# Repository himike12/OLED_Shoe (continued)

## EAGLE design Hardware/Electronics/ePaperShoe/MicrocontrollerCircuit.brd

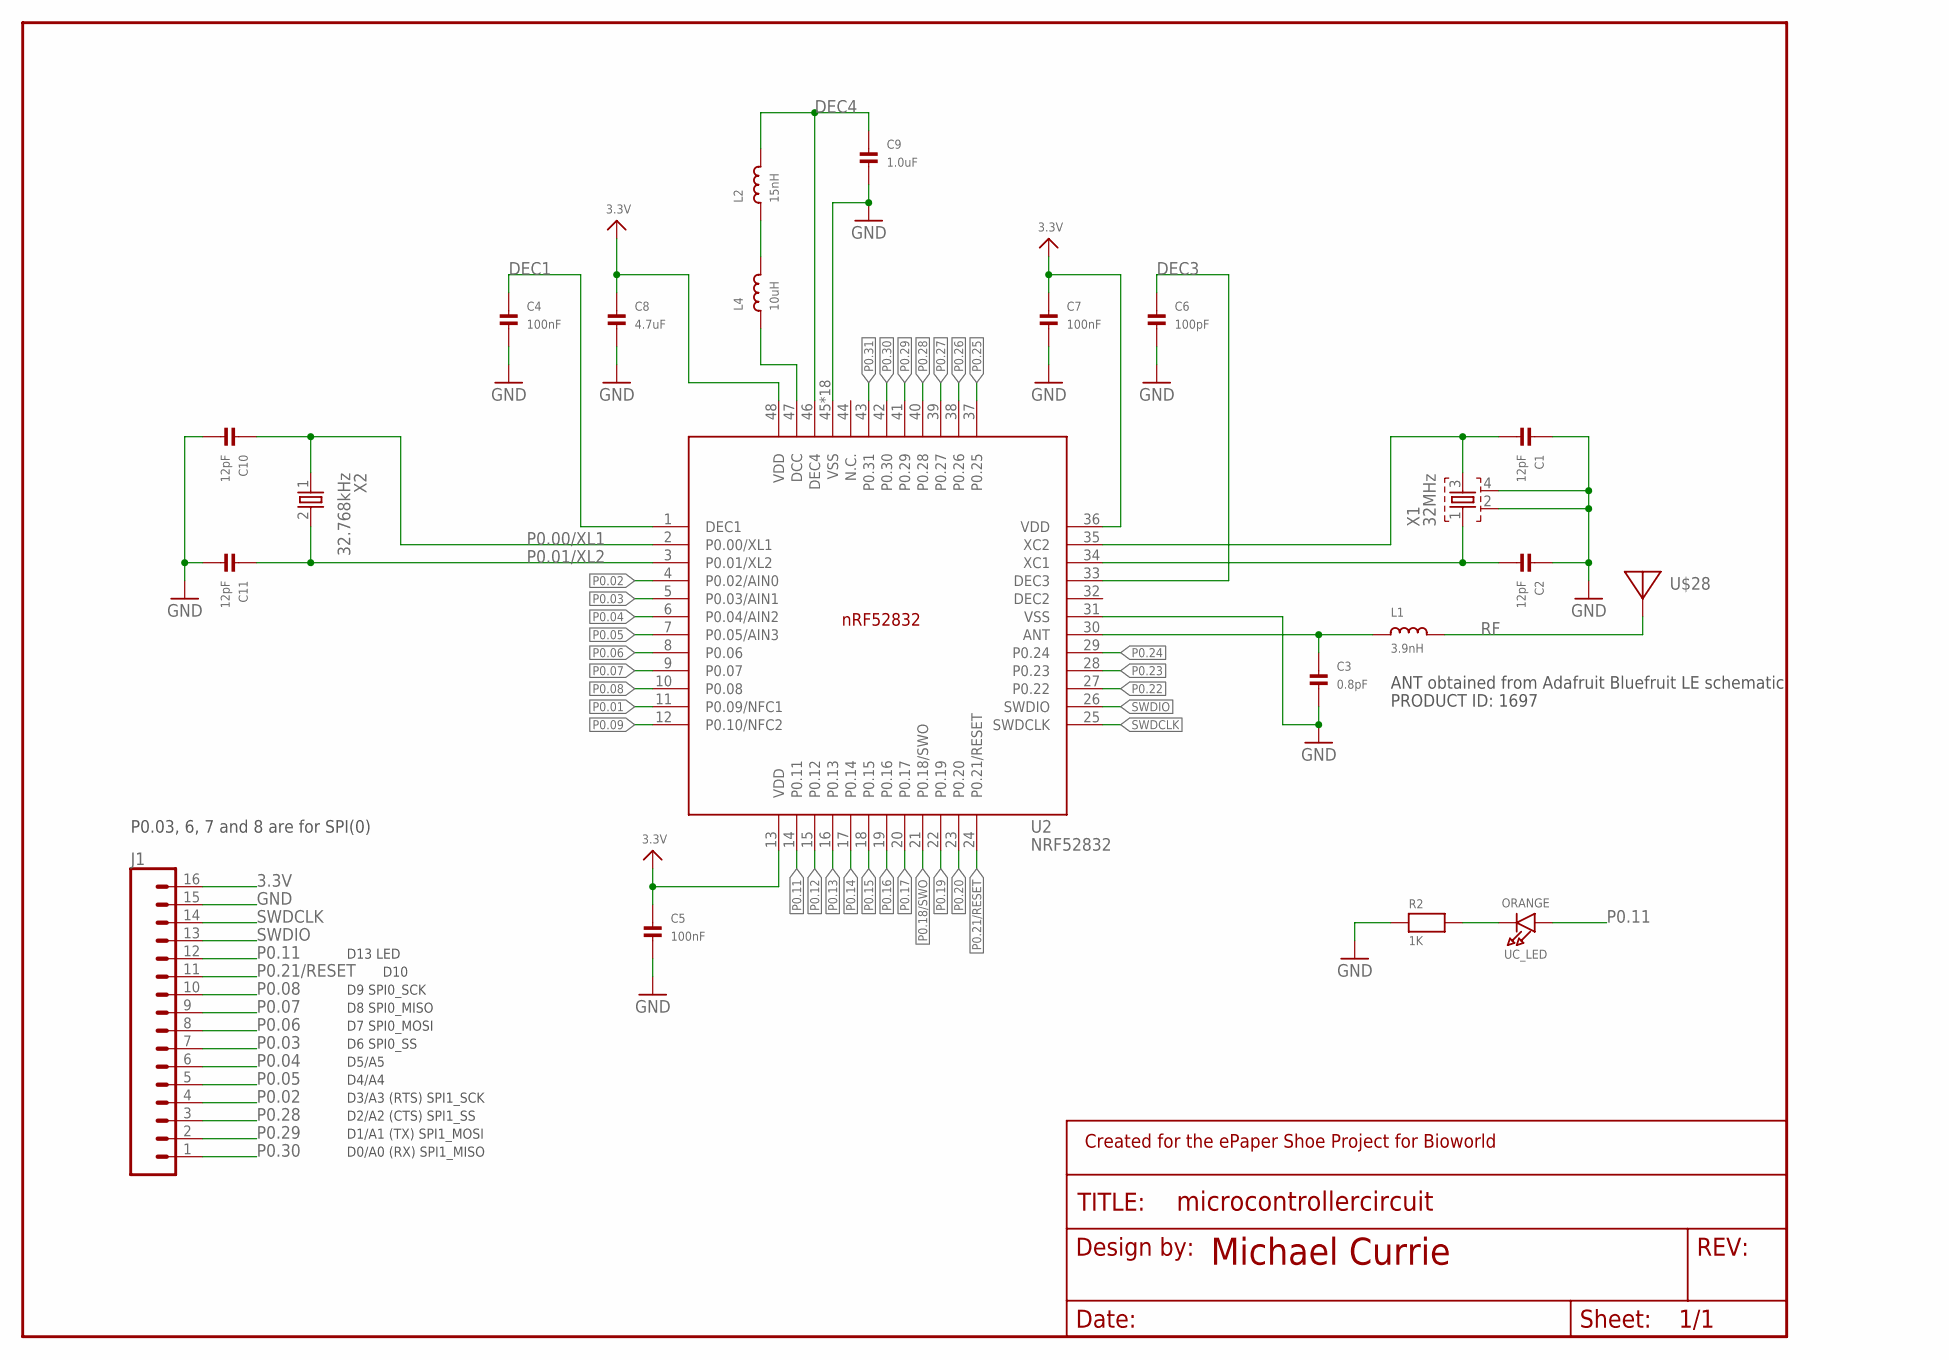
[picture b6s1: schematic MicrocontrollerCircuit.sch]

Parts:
C1, C2, C10, C11: 12pF; 1206
C3: 0.8pF; 1206
C4, C5, C7: 100nF; 1206
C6: 100pF; 1206
C8: 4.7uF; 1206
C9: 1.0uF; 1206
FRAME2: FRAME-LETTER-MICHAELNO_PACKAGE; DUMMY
J1: CONN_16; 1X16
L1: 3.9nH; 0805
L2: 15nH; 0805
L4: 10uH; 0805
R2: 1K; 0805
U2: NRF52832; QFN40P600X600X90-48_N
U$28: ANTENNA_PCBNRF8001_1.6MM; ANT_PCB_2.4GHZ_NRF8001_1.6MM_1OZ
UC_LED: ORANGE; CHIPLED_0805_NOOUTLINE
X1: 32MHz; BT-XTAL_2016_N
X2: 32.768kHz; XTAL_3215_N

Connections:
3.3V: C5.1, C7.1, C8.1, J1.16, U2.13 (VDD), U2.36 (VDD), U2.48 (VDD)
ANT: C3.1, L1.1, U2.30 (ANT)
DEC1: C4.1, U2.1 (DEC1)
DEC3: C6.1, U2.33 (DEC3)
DEC4: C9.1, L2.2, U2.46 (DEC4)
GND: C1.1, C2.1, C3.2, C4.2, C5.2, C6.2, C7.2, C8.2, C9.2, C10.2, C11.2, J1.15, R2.1, U2.31 (VSS), U2.45 (VSS), U2.PAD (VSS), U2.PAD@VIA01 (VSS), U2.PAD@VIA02 (VSS), U2.PAD@VIA03 (VSS), U2.PAD@VIA04 (VSS), U2.PAD@VIA05 (VSS), U2.PAD@VIA06 (VSS), U2.PAD@VIA07 (VSS), U2.PAD@VIA08 (VSS), U2.PAD@VIA09 (VSS), U2.PAD@VIA10 (VSS), U2.PAD@VIA11 (VSS), U2.PAD@VIA12 (VSS), U2.PAD@VIA13 (VSS), U2.PAD@VIA14 (VSS), U2.PAD@VIA15 (VSS), U2.PAD@VIA16 (VSS), X1.2, X1.4
unnamed: L2.1, L4.2
unnamed: C1.2, U2.35 (XC2), X1.3
unnamed: L4.1, U2.47 (DCC)
unnamed: R2.2, UC_LED.C
P0.00/XL1: C10.1, U2.2 (P0.00/XL1), X2.1
P0.01: U2.11 (P0.09/NFC1)
P0.01/XL2: C11.1, U2.3 (P0.01/XL2), X2.2
P0.02: J1.4, U2.4 (P0.02/AIN0)
P0.03: J1.7, U2.5 (P0.03/AIN1)
P0.04: J1.6, U2.6 (P0.04/AIN2)
P0.05: J1.5, U2.7 (P0.05/AIN3)
P0.06: J1.8, U2.8 (P0.06)
P0.07: J1.9, U2.9 (P0.07)
P0.08: J1.10, U2.10 (P0.08)
P0.09: U2.12 (P0.10/NFC2)
P0.11: J1.12, U2.14 (P0.11), UC_LED.A
P0.12: U2.15 (P0.12)
P0.13: U2.16 (P0.13)
P0.14: U2.17 (P0.14)
P0.15: U2.18 (P0.15)
P0.16: U2.19 (P0.16)
P0.17: U2.20 (P0.17)
P0.18/SWO: U2.21 (P0.18/SWO)
P0.19: U2.22 (P0.19)
P0.20: U2.23 (P0.20)
P0.21/RESET: J1.11, U2.24 (P0.21/RESET)
P0.22: U2.27 (P0.22)
P0.23: U2.28 (P0.23)
P0.24: U2.29 (P0.24)
P0.25: U2.37 (P0.25)
P0.26: U2.38 (P0.26)
P0.27: U2.39 (P0.27)
P0.28: J1.3, U2.40 (P0.28)
P0.29: J1.2, U2.41 (P0.29)
P0.30: J1.1, U2.42 (P0.30)
P0.31: U2.43 (P0.31)
RF: L1.2, U$28.FEED
SWDCLK: J1.14, U2.25 (SWDCLK)
SWDIO: J1.13, U2.26 (SWDIO)
X1: C2.2, U2.34 (XC1), X1.1

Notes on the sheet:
P0.03, 6, 7 and 8 are for SPI(0)
ANT obtained from Adafruit Bluefruit LE schematic
PRODUCT ID: 1697
D1/A1 (TX) SPI1_MOSI
D0/A0 (RX) SPI1_MISO
D2/A2 (CTS) SPI1_SS
D3/A3 (RTS) SPI1_SCK
D4/A4
D5/A5
D6 SPI0_SS
D7 SPI0_MOSI
D8 SPI0_MISO
D9 SPI0_SCK
D10
D13 LED

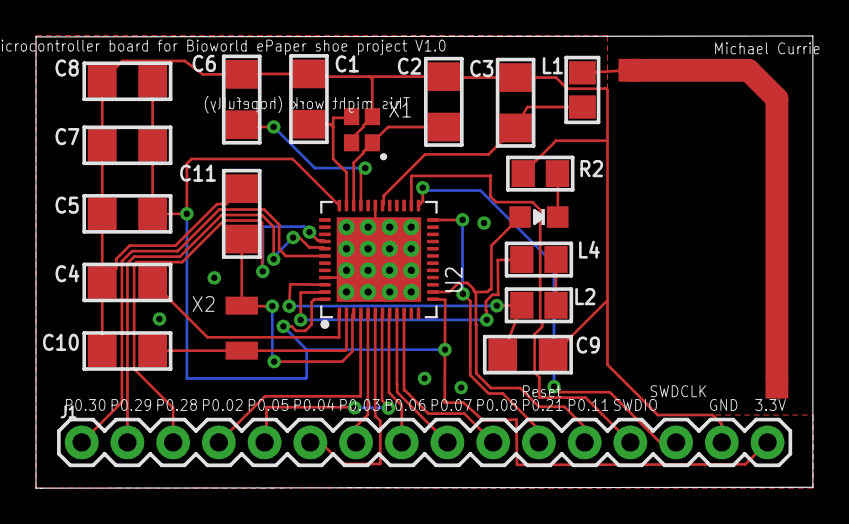
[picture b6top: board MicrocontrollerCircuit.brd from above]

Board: 2 copper layers, 43.2 x 25.1 mm, 22 parts (0 on the bottom side), 28 nets.

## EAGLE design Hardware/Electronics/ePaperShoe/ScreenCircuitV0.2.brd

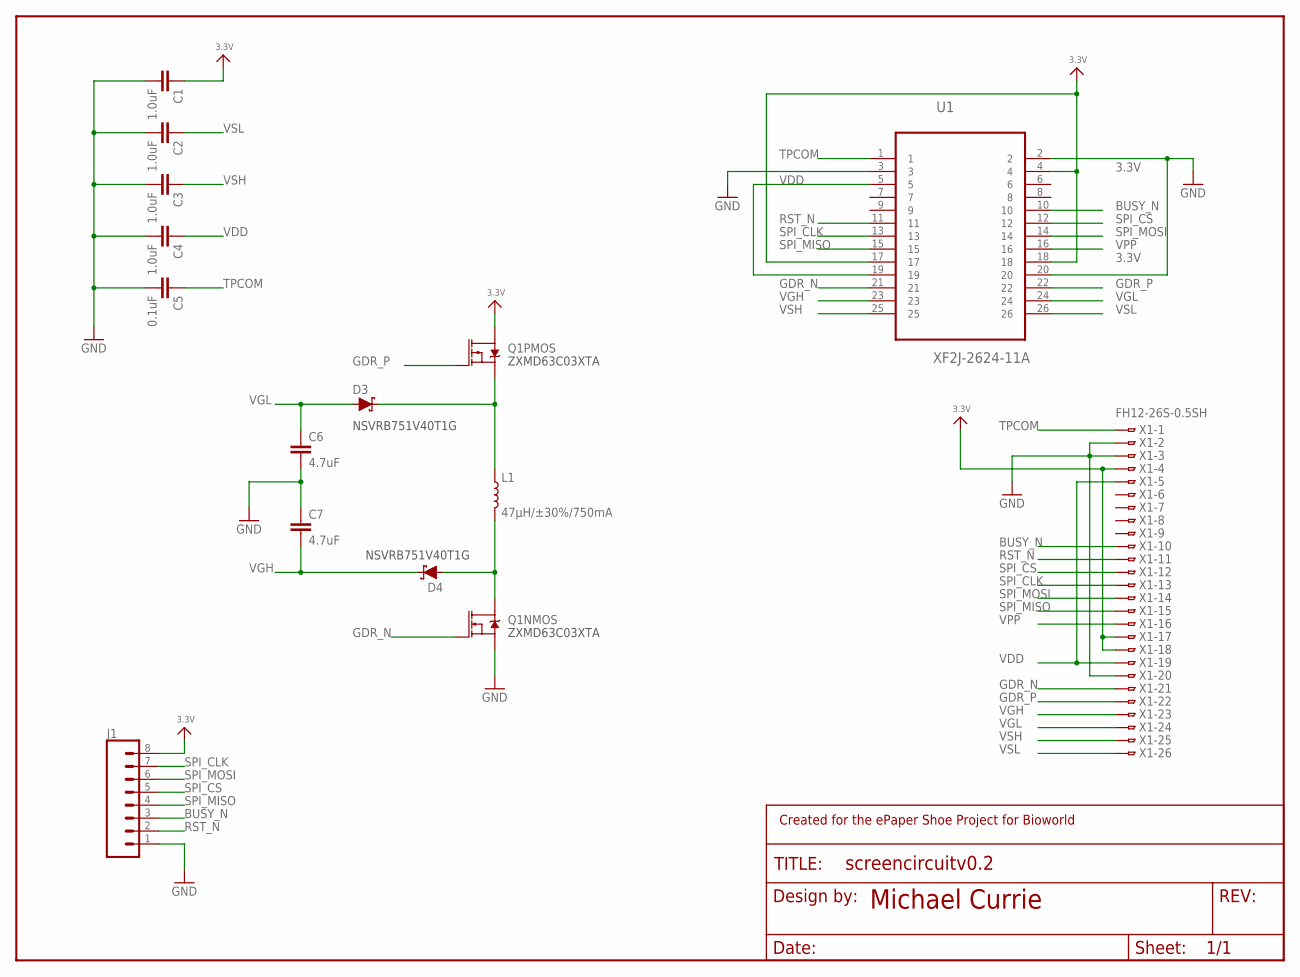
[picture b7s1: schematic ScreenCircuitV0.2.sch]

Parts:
C1, C2, C3, C4: 1.0uF; 1206
C5: 0.1uF; 0603
C6, C7: 4.7uF; 1206
D3, D4: 0.5A/40V/420mV; SOD-323
FRAME1: FRAME-LETTER-MICHAELNO_PACKAGE; DUMMY
J1: CONN_08"; 1X08
L1: 47µH/±30%/750mA; CR54
Q1: IRF7509; MSOP8
U1: XF2J-2624-11A; OMRON_XF2J-2624-11A
X1: FH12-26S-0.5SH

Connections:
3.3V: C1.1, J1.8, Q1.5 (D), Q1.6 (D), U1.4, U1.17, U1.18, X1.4, X1.17, X1.18
BUSY_N: J1.3, U1.10, X1.10
GDR_N: Q1.2 (G), U1.21, X1.21
GDR_P: Q1.4 (G), U1.22, X1.22
GND: C1.2, C2.2, C3.2, C4.2, C5.2, C6.2, C7.1, J1.1, Q1.1 (S), U1.2, U1.3, U1.20, X1.2, X1.3, X1.20
unnamed: D3.C, L1.P$1 (1), Q1.3 (S)
unnamed: D4.A, L1.P$2 (2), Q1.7 (D), Q1.8 (D)
RST_N: J1.2, U1.11, X1.11
SPI_CLK: J1.7, U1.13, X1.13
SPI_CS: J1.5, U1.12, X1.12
SPI_MISO: J1.4, U1.15, X1.15
SPI_MOSI: J1.6, U1.14, X1.14
TPCOM: C5.1, U1.1, X1.1
VDD: C4.1, U1.5, U1.19, X1.5, X1.19
VGH: C7.2, D4.C, U1.23, X1.23
VGL: C6.1, D3.A, U1.24, X1.24
VPP: U1.16, X1.16
VSH: C3.1, U1.25, X1.25
VSL: C2.1, U1.26, X1.26

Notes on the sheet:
ZXMD63C03XTA
NSVRB751V40T1G

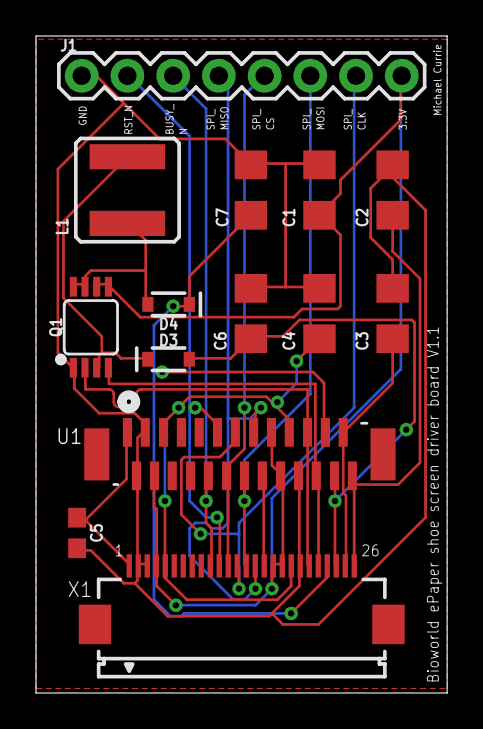
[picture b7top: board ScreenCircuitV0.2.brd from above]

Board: 2 copper layers, 22.8 x 36.5 mm, 15 parts (0 on the bottom side), 19 nets.

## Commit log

2017-09-13 edited the readme
2017-10-22 Added New Page
2017-10-22 Images on Home Screen
2017-10-22 Images on Home Screen v2
2017-10-22 Images v3
2017-10-22 Images v4
2017-10-22 Tutorial
2017-10-22 Tutorial v2
2017-10-22 Tutorial v3
2017-10-22 Tutorial v4
2017-10-22 Added some new UI
2017-10-22 Added Loop Functionality to Pictures
2017-10-23 Working on UI/UX
2017-10-23 Title Bar Fix
2017-10-23 More Padding to Title Bar
2017-10-23 Title Bar Final
2017-10-23 Spot for Selected Picture Added
2017-10-23 Renamed Pages
2017-10-24 Splash Screen
2017-10-24 Removed Splash Screen, too many errors
2017-10-24 Added BioWorld Pic
2017-10-24 Splash Screen v1
2017-10-24 Splash Screen v2
2017-10-24 Splash Screen v3
2017-10-24 Splash Screen v4
2017-10-24 Splash Screen v5
2017-10-24 Splash Screen v6
2017-10-31 Picture Library v1
2017-10-31 Picture Library v2
2017-10-31 Splash Screen v7
2017-10-31 Splash Screen v8
2017-10-31 Splash screen v9
2017-10-31 Splash Screen v10
2017-10-31 Splash Screen v11
2017-10-31 Splash Screen v12
2017-10-31 Splash Screen v13
2017-10-31 Splash Screen v14
2017-11-04 Added BLE serial programs for the nRF52
2017-11-04 Little update to BLE_module README file
2017-11-07 Changed serial speed to 9600 to support the DAPLink
2017-11-08 Reordered files and added files from PlasticLogic SD card
2017-11-10 Started schematic and added power circuits
2017-11-10 Made Red Bear LED alternate between on and off when recieving a byte over BLE UART
2017-11-10 Added designes from Adafruit for some parts purchased from them
2017-11-11 Update hello-ionic.html
    Added the HTML Button - select image
2017-11-11 Update hello-ionic.ts
    Added the Functionality for 'Select an Image' button
2017-11-15 Update config.xml
    Fixed Error
2017-11-17 added circuit for driving screen
2017-11-23 Changes made to the screen circuit
2017-11-25 small update
2017-11-28 New Git Pull
2017-11-28 Install promise-polyfill
2017-12-04 Trying to push
2017-12-04 Reinstalled npm
2017-12-04 Package plus import statement
2017-12-04 Angular added
2017-12-04 Package
2017-12-04 Made screen circuit version 0.2
2017-12-04 New modules
2017-12-04 Changed tslint.json
2017-12-04 Added new packages
2017-12-06 Click to ng-click
2017-12-06 Reverted to click, added tappable
2017-12-06 Added Alert Controller, other things
2017-12-06 Packages galore
2017-12-06 Added Bluetooth page
2017-12-06 Added Bluetooth
2017-12-06 Bluetooth Scan Fix
2017-12-06 BLE 1.0
2017-12-06 Added Menu to Bluetooth Page
2017-12-06 BLE 1.1, Added Connect Feature
2017-12-06 BLE 1.2, Connect + Disconnect
2017-12-06 BLE 1.3, Removed alerts
2017-12-06 BLE 1.4, Status Message for Connection. Removed alerts from homepage
2017-12-07 BLE 1.5, Disconnected Message
2018-01-10 Attempt on screen driver and PCB design for Nordic chip
2018-01-17 Finished design on the nRF52 schematic
2018-01-23 Minor adjustments to the to nRF52 PCB
2018-01-25 Finished design of microcontroller circuit and added logic analyser snapshots
2018-01-26 moved file to new location
2018-01-26 Removed duplicate content in headder file
2018-01-26 Facebook
2018-01-26 Facebook login done
2018-01-26 Removed excess content in headder file
2018-01-26 Added packages
2018-01-30 Added Paperino Arduino example code
2018-02-07 Added SD card contents from PlasticLogic wide screen
2018-02-08 Facebook Debug v1
2018-02-08 Added Error Monitoring
2018-02-08 Error Monitoring v2
2018-02-08 Test Button on Facebook Page
2018-02-08 Button works, something wrong with opening Facebook
2018-02-08 See if button works for Facebook
2018-02-08 Aakash's Facebook V1
2018-02-08 Back to Normal
2018-02-08 New Packages and Content-Security-Policy
2018-02-14 Worling screen with uC and image conversion example code
2018-02-15 The screen is working with the nrf52-DK and Can display images with 4 Levels of gray
2018-02-19 Added Alert for Error
2018-02-19 New Cordova Plugin
2018-02-19 Removed and Added Packages
2018-02-22 Firebase config
2018-02-22 Firebase Duplicate Error
2018-02-22 debugging Firebase Error
2018-03-01 Screen is working with bluetooth. Did some file sorting
2018-03-01 Made demo program that will take commands from bluetooth and display
2018-03-03 Created Connector board to conect the screen to a ribbon cable
2018-03-05 Designed new screen board and made minor changes to the connector board
2018-03-11 Added README.md files to all of the apropriate directories in the Hardware folder
2018-03-19 Rohan
2018-03-19 Change Package details
2018-03-19 Removed package-lock
2018-03-19 Changed app.module.ts
2018-03-24 Added Firebase package
2018-03-24 Firebase with Gallery
2018-03-24 Gallery with Firebase
2018-03-27 Alert with service ID's
2018-03-27 Services[1]
2018-03-27 Characteristics
2018-03-27 JSON Stringify Characteristics
2018-03-28 BLE Write v1
2018-03-28 Updated Packages
2018-03-28 BLE Write v2
2018-03-28 BLE Write v3
2018-04-04 New packages
2018-04-04 Added Ionic Pro Package
2018-04-04 Took out BLE Write Line
2018-04-04 Added BLUETOOTH_USAGE_DESCRIPTION Variable
2018-04-04 Changed Buffer
2018-04-04 Changed Var to Let
2018-04-09 Version 1.0 for Teensy game of life
2018-04-10 Designed microcontroller board V2 and USB board
2018-04-11 Completed final schematic diagram, started PCD design
2018-04-11 Completed layout and traces of PCB. Need to still add silkscreen and arrange lables
2018-04-12 Completed PCB with everything on it V1.0
2018-04-25 iOS App v1
2018-04-27 No crash
2018-04-28 Changes here and there, refining the product
2018-04-29 BLE v1
2018-04-29 New Scan
2018-04-29 startScan
2018-04-29 Changed back
2018-04-30 Android feature
2018-05-01 added images for the poster
